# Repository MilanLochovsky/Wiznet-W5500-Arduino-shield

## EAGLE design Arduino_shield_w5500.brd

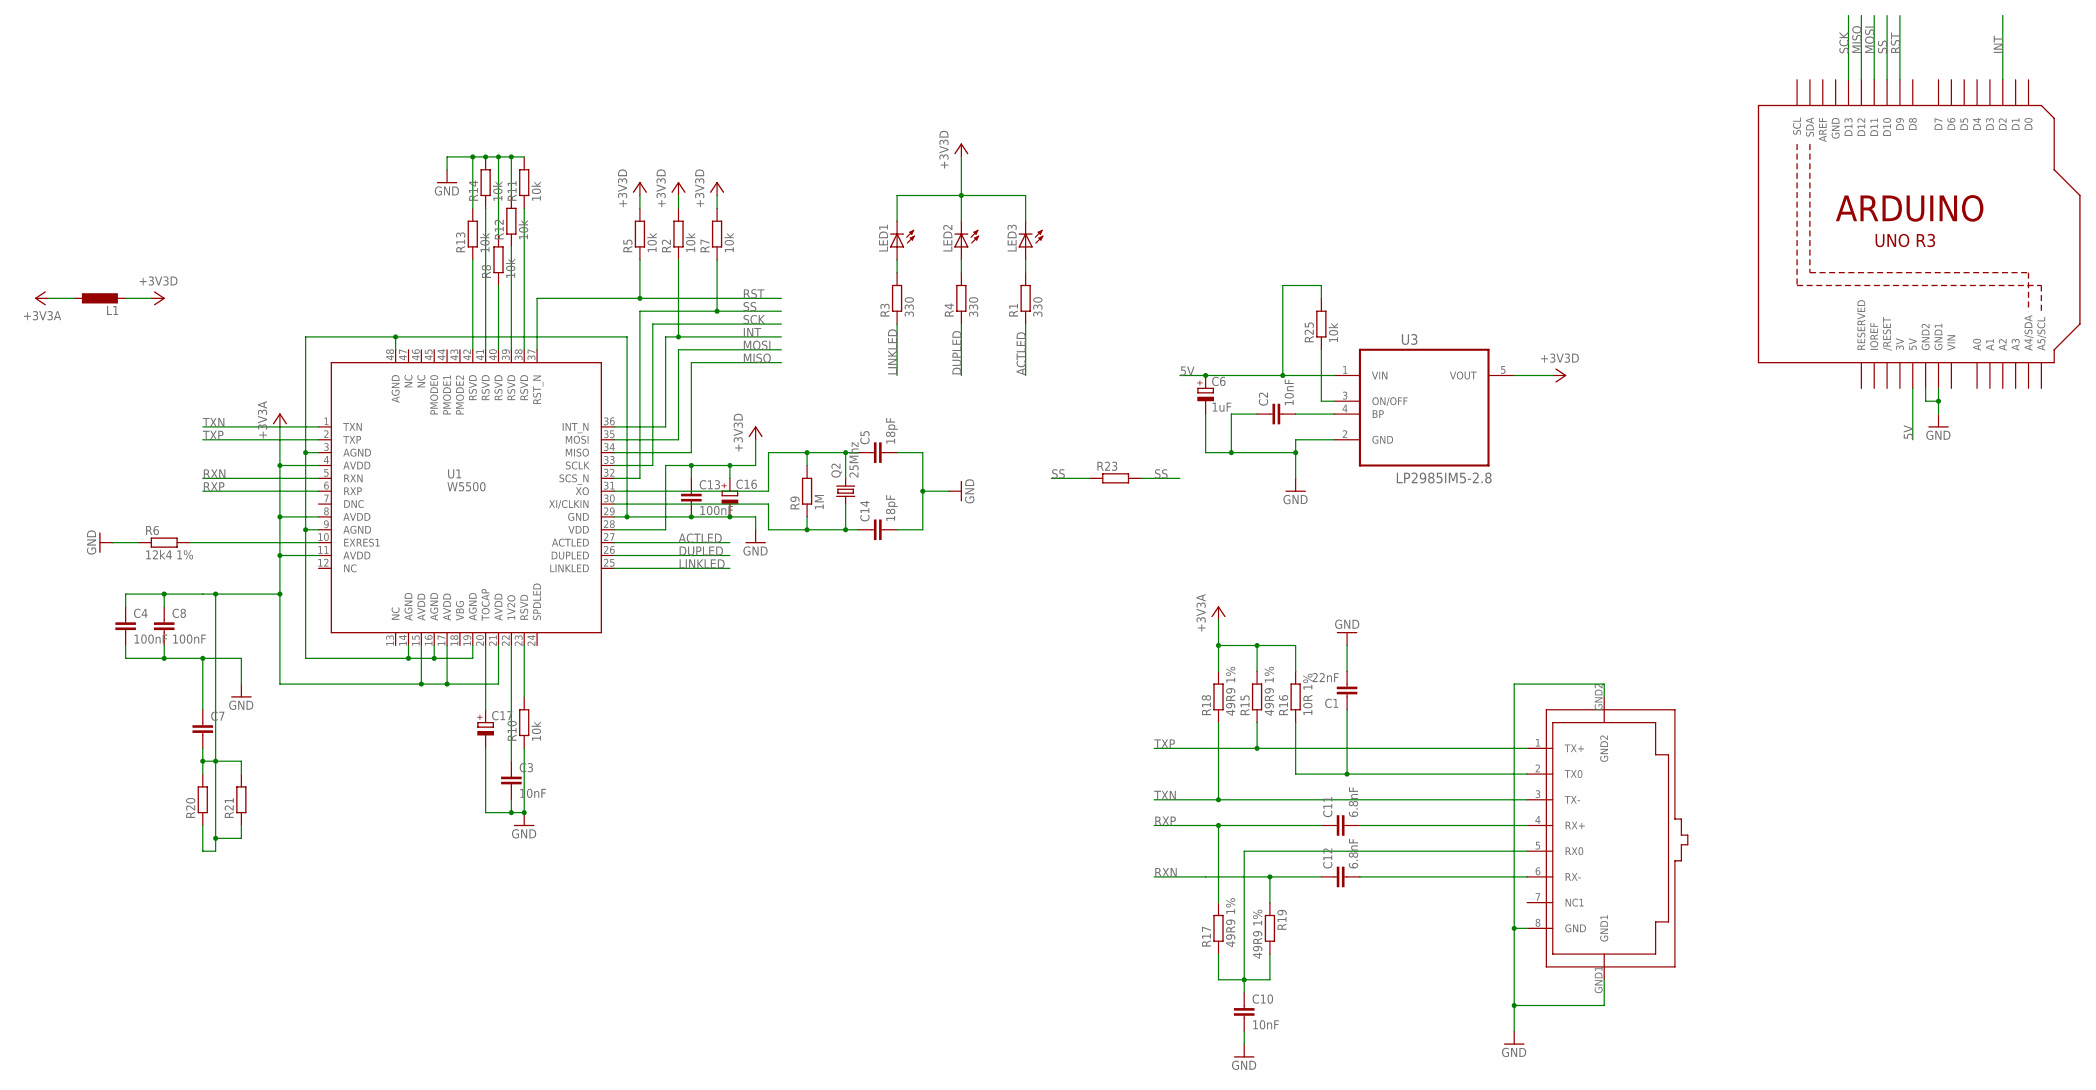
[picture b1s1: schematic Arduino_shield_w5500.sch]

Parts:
C1: 22nF; C1206K
C2: 10nF; C1206
C3, C10: 10nF; C1206K
C4, C8, C13: 100nF; C1206K
C5, C14: 18pF; C1206K
C6: 1uF; 153CLV-0405
C7: C-EUC1206; C1206
C11, C12: 6.8nF; C1206K
C16: CPOL-EU153CLV-0505; 153CLV-0505
C17: CPOL-EU153CLV-0405; 153CLV-0405
L1: L-EUL3225M; L3225M
LED1, LED2, LED3: LED3MM
Q2: 25Mhz; CTS406
R1, R3, R4: 330; R1206W
R2, R5, R7, R8, R10, R11, R12, R13, R14, R25: 10k; R1206W
R6: 12k4 1%; R1206W
R9: 1M; R1206W
R15, R17, R18, R19: 49R9 1%; R1206W
R16: 10R 1%; R1206W
R20, R21, R23: R-EU_R1206W; R1206W
U1: W5500
U2: ARDUINOR3-DIMENSION; ARDUINOR3
U3: LP2985IM5-2.8; SOT95P284X120-5N
U$2: RJ45-TRAFO

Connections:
3V: U2.3V
5V: C6.+, R25.2, U2.5V, U3.1 (VIN)
+3V3: U3.5 (VOUT)
+3V3A: C4.1, C7.2, C8.1, L1.1, R15.2, R16.2, R18.2, R20.1, R20.2, R21.1, R21.2, U1.4 (AVDD), U1.8 (AVDD), U1.11 (AVDD), U1.15 (AVDD), U1.17 (AVDD), U1.21 (AVDD)
+3V3D: C13.1, C16.+, L1.2, LED1.K (C), LED2.K (C), LED3.K (C), R2.2, R5.2, R7.2, U1.28 (VDD)
ACTLED: R1.1, U1.27 (ACTLED)
DUPLED: R4.1, U1.26 (DUPLED)
GND: C1.2, C2.1, C3.2, C4.2, C5.2, C6.-, C8.2, C10.2, C13.2, C14.2, C16.-, C17.-, R6.1, R8.2, R10.1, R11.2, R12.2, R13.2, R14.2, U1.3 (AGND), U1.9 (AGND), U1.14 (AGND), U1.16 (AGND), U1.19 (AGND), U1.29 (GND), U1.48 (AGND), U2.GND, U2.GND1, U2.GND2, U3.2 (GND), U$2.8 (GND), U$2.GND1, U$2.GND2
INT: R2.1, U1.36 (INT_N), U2.D2
LINKLED: R3.1, U1.25 (LINKLED)
MISO: U1.34 (MISO), U2.D12
MOSI: U1.35 (MOSI), U2.D11
unnamed: R13.1, U1.42 (RSVD)
unnamed: LED1.A, R3.2
unnamed: R14.1, U1.41 (RSVD)
unnamed: R8.1, U1.40 (RSVD)
unnamed: R12.1, U1.39 (RSVD)
unnamed: R11.1, U1.38 (RSVD)
unnamed: R10.2, U1.23 (RSVD)
unnamed: C3.1, U1.22 (1V2O)
unnamed: LED2.A, R4.2
unnamed: C5.1, Q2.3 (2), R9.2, U1.31 (XO)
unnamed: C14.1, Q2.1, R9.1, U1.30 (XI/CLKIN)
unnamed: R6.2, U1.10 (EXRES1)
unnamed: LED3.A, R1.2
unnamed: C11.2, U$2.4 (RX+)
unnamed: C1.1, R16.1, U$2.2 (TX0)
unnamed: C17.+, U1.20 (TOCAP)
unnamed: C10.1, R17.1, R19.2, U$2.5 (RX0)
unnamed: C12.2, U$2.6 (RX-)
unnamed: C2.2, U3.4 (BP)
unnamed: R25.1, U3.3 (ON/OFF)
RST: R5.1, U1.37 (RST_N), U2.D9
RXN: C12.1, R19.1, U1.5 (RXN)
RXP: C11.1, R17.2, U1.6 (RXP)
SCK: U1.33 (SCLK), U2.D13
SS: R7.1, R23.1, R23.2, U1.32 (SCS_N), U2.D10
TXN: R18.1, U1.1 (TXN), U$2.3 (TX-)
TXP: R15.1, U1.2 (TXP), U$2.1 (TX+)
VIN: U2.VIN

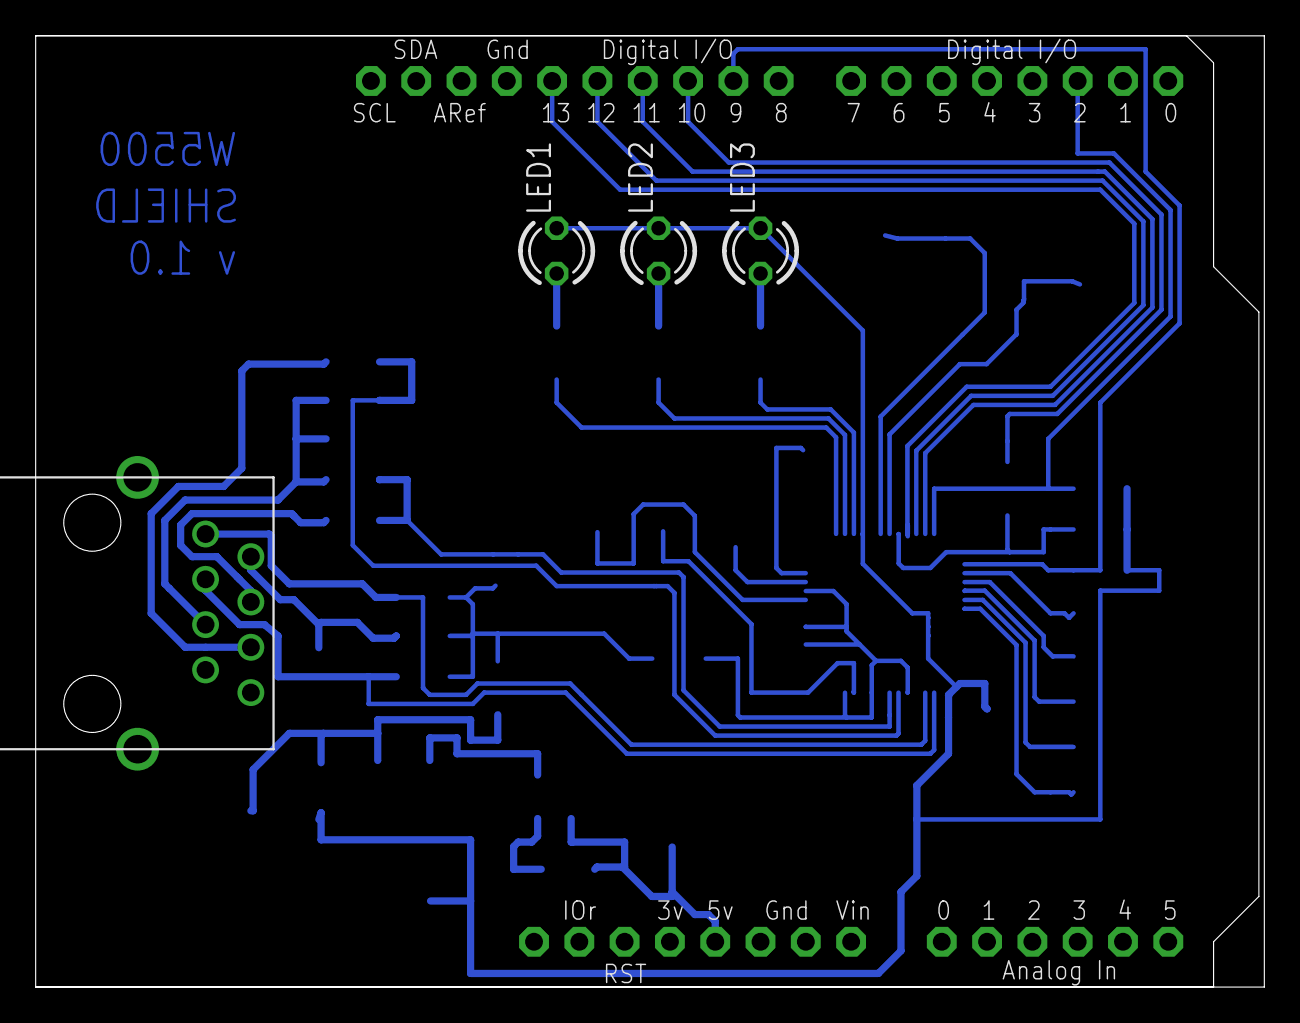
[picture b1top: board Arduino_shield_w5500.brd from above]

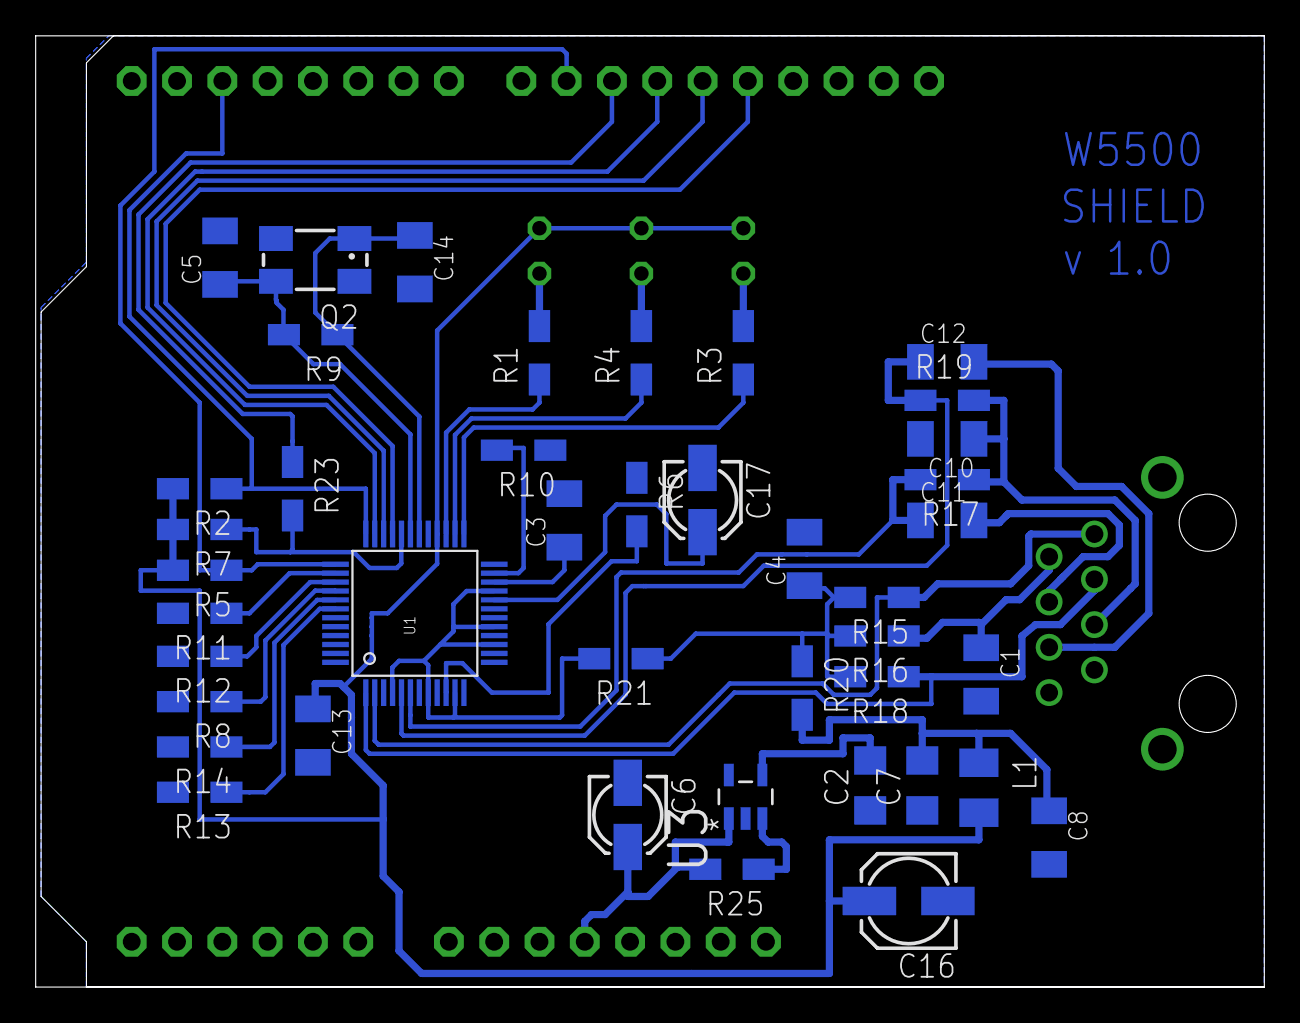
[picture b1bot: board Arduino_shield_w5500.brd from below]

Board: 2 copper layers, 68.9 x 53.3 mm, 47 parts (42 on the bottom side), 37 nets.

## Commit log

2016-01-06 :lollipop: Added .gitattributes & .gitignore files
2016-01-06 init version
